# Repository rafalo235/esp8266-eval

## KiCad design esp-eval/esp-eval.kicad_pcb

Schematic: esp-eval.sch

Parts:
C1: 47u; CP_Radial_D6.3mm_P2.50mm
C2: 220u; CP_Radial_D8.0mm_P5.00mm
C3: 100n; C_Disc_D3.0mm_W1.6mm_P2.50mm
J1: ESP-ADAPT-1; Pin_Header_Straight_1x12_Pitch2.54mm
J2: ESP-ADAPT-2; Pin_Header_Straight_1x12_Pitch2.54mm
J3: ESP-ADAPT-1-DBG; Pin_Header_Straight_1x12_Pitch2.54mm
J4: ESP-ADAPT-2-DBG; Pin_Header_Straight_1x12_Pitch2.54mm
J5: GPIO0-SEL; Pin_Header_Straight_1x03_Pitch2.54mm
J6: GPIO2-SEL; Pin_Header_Straight_1x03_Pitch2.54mm
J7: GPIO15-SEL; Pin_Header_Straight_1x03_Pitch2.54mm
J8: USB-FTDI; Pin_Header_Straight_1x04_Pitch2.54mm
R1, R2, R3, R4, R5, R6, R7, R8, R9: 10k; R_0805_HandSoldering
SW1: SW-GPIO0; SW_PUSH_6mm
SW2: SW-RST; SW_PUSH_6mm
U1: MCP1700-3302E_SOT23; SOT-23

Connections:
+3V3: C2.1, C3.1, J2.1, J4.1, R1.1, R2.1, R3.1, R5.1, R6.1, R8.1, U1.2 (VO)
/ADC: J2.7, J4.7
/CS0: J1.2, J3.2
/EN: J2.6, J4.6, R5.2
/GPIO0: J1.10, J3.10, J5.2, R1.2, SW1.1
/GPIO2: J1.9, J3.9, J6.2
/GPIO4: J1.11, J3.11
/GPIO5: J1.12, J3.12
/GPIO9: J1.6, J3.6
/GPIO10: J1.7, J3.7
/GPIO12: J2.3, J4.3
/GPIO13: J2.2, J4.2
/GPIO14: J2.4, J4.4
/GPIO15: J1.8, J3.8, J7.2
/GPIO16: J2.5, J4.5
/MISO: J1.3, J3.3
/MOSI: J1.4, J3.4
/RST: J2.8, J4.8, R2.2, SW2.1
/RXD0: J2.9, J4.9, J8.3
/SCLK: J1.5, J3.5
/TXD0: J2.10, J4.10, J8.2
GND: C1.2, C2.2, C3.2, J1.1, J3.1, J8.4, R4.2, R7.2, R9.2, SW1.2, SW2.2, U1.1 (GND); also elsewhere on the board
unnamed: J2.11, J4.11
unnamed: J2.12, J4.12
unnamed: J5.1, R3.2
unnamed: J5.3, R4.1
unnamed: J6.1, R6.2
unnamed: J6.3, R7.1
unnamed: J7.1, R8.2
unnamed: J7.3, R9.1
VBUS: C1.1, J8.1, U1.3 (VI)

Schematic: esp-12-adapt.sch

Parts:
J9: ESP-ADAPT-1-SHIELD; Pin_Header_Straight_1x12_Pitch2.54mm
J10: ESP-ADAPT-2-SHIELD; Pin_Header_Straight_1x12_Pitch2.54mm
U2: ESP-12E; ESP-12E_SMD

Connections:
/esp-12-adapt/ADC: J10.7, U2.2
/esp-12-adapt/CS0: J9.2, U2.17
/esp-12-adapt/EN: J10.6, U2.3
/esp-12-adapt/GPIO0: J9.10, U2.12
/esp-12-adapt/GPIO2: J9.9, U2.11
/esp-12-adapt/GPIO4: J9.11, U2.13
/esp-12-adapt/GPIO5: J9.12, U2.14
/esp-12-adapt/GPIO9: J9.6, U2.19
/esp-12-adapt/GPIO10: J9.7, U2.20
/esp-12-adapt/GPIO12: J10.3, U2.6
/esp-12-adapt/GPIO13: J10.2, U2.7
/esp-12-adapt/GPIO14: J10.4, U2.5
/esp-12-adapt/GPIO15: J9.8, U2.10
/esp-12-adapt/GPIO16: J10.5, U2.4
/esp-12-adapt/MISO: J9.3, U2.18
/esp-12-adapt/MOSI: J9.4, U2.21
/esp-12-adapt/RST: J10.8, U2.1
/esp-12-adapt/RXD0: J10.9, U2.15
/esp-12-adapt/SCLK: J9.5, U2.22
/esp-12-adapt/TXD0: J10.10, U2.16
/esp-12-adapt/VCC: J10.1, U2.8
GND: J9.1, U2.9; also elsewhere on the board

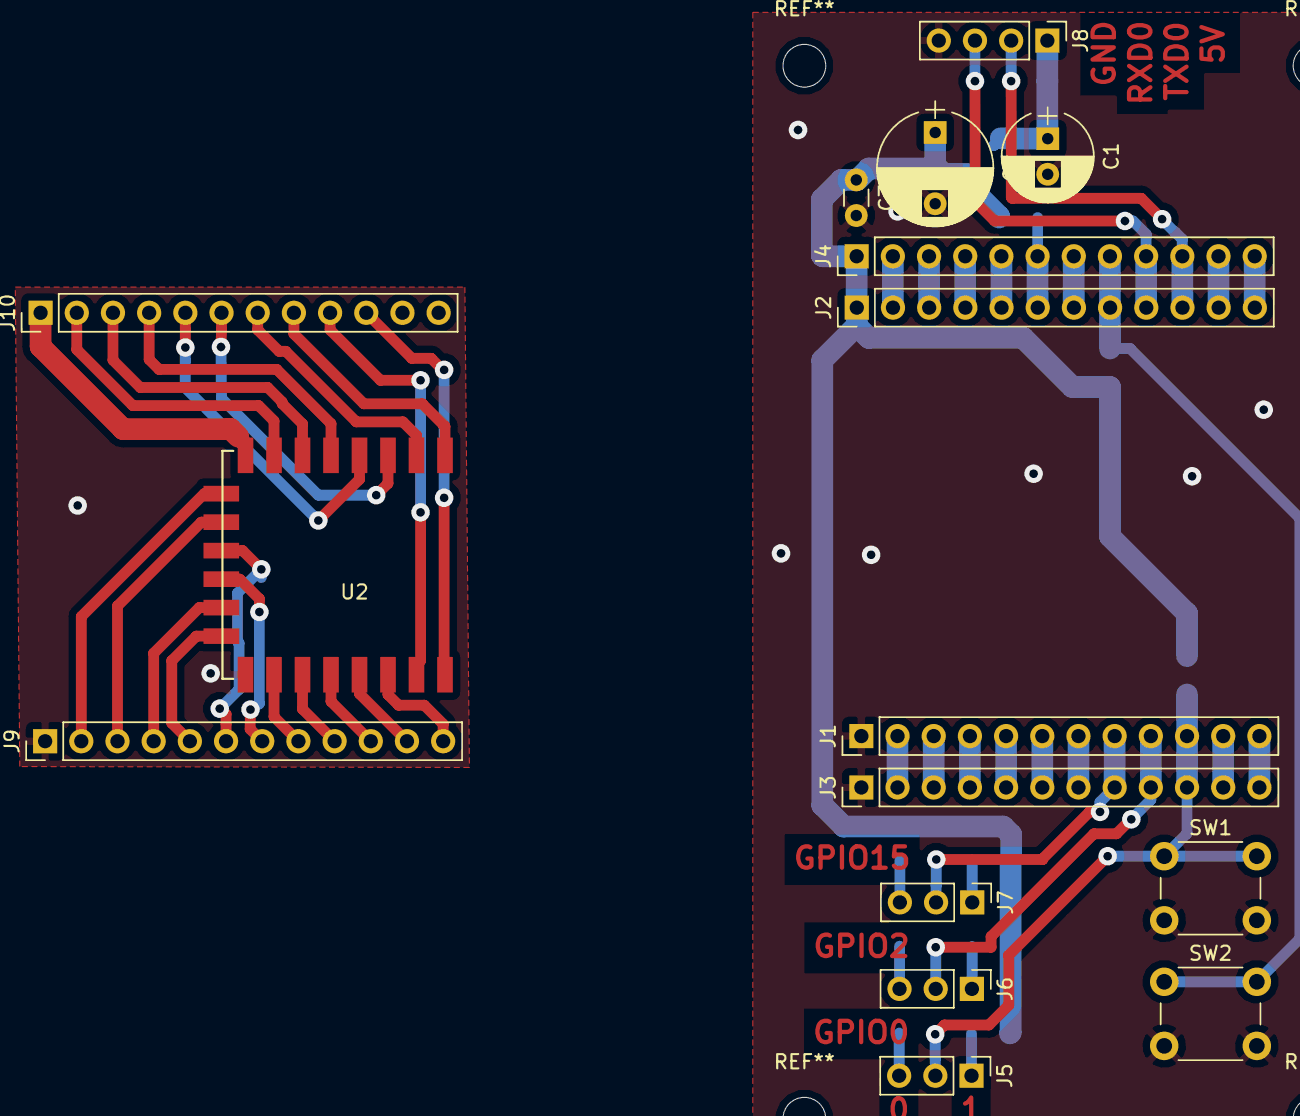
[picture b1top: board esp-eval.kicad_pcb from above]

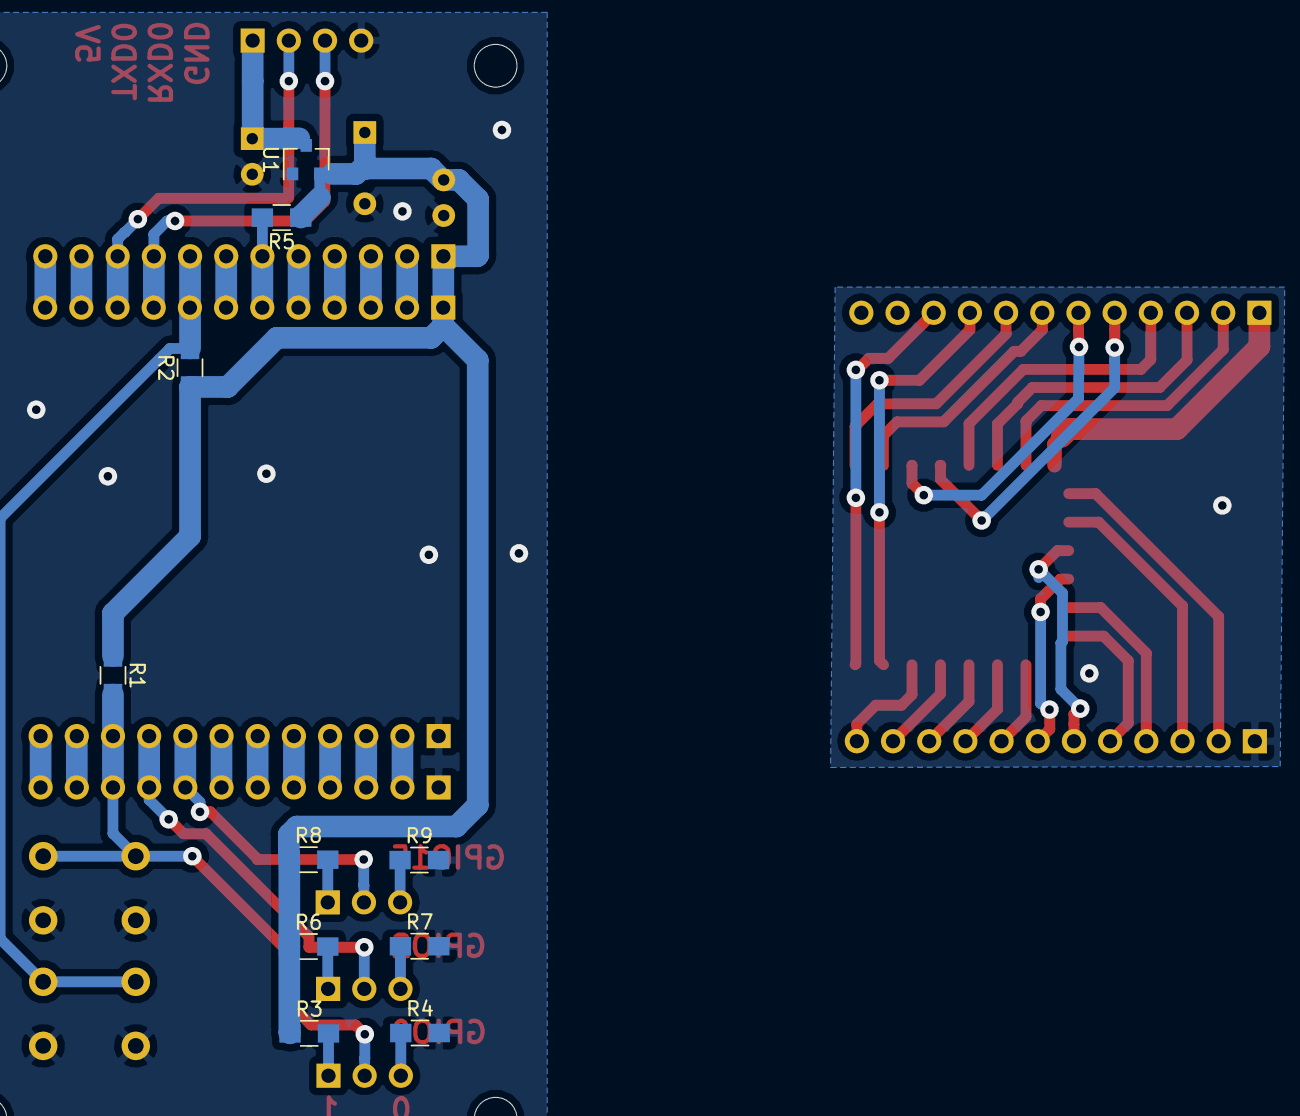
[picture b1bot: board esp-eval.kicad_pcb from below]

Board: 2 copper layers, 26 parts (10 on the bottom side), 52 nets.

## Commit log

2018-10-16 init commit
2018-10-16 pcb rule check
2018-10-16 przelotak gnd na plytce adapt
2018-10-16 dokumentacja
2018-10-16 otwory montazowe
2018-10-16 ulozenie plytek
2018-10-16 nity pcb
2018-10-19 wymiary
2018-10-23 napisy
2021-06-20 fixes;
2021-06-20 license
